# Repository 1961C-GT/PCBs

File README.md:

# PCBs
A Repo for storing all PCB designs for the project

# Library
All collaborative eagle library items should be stored in a .lbr file located in ./Libraries.

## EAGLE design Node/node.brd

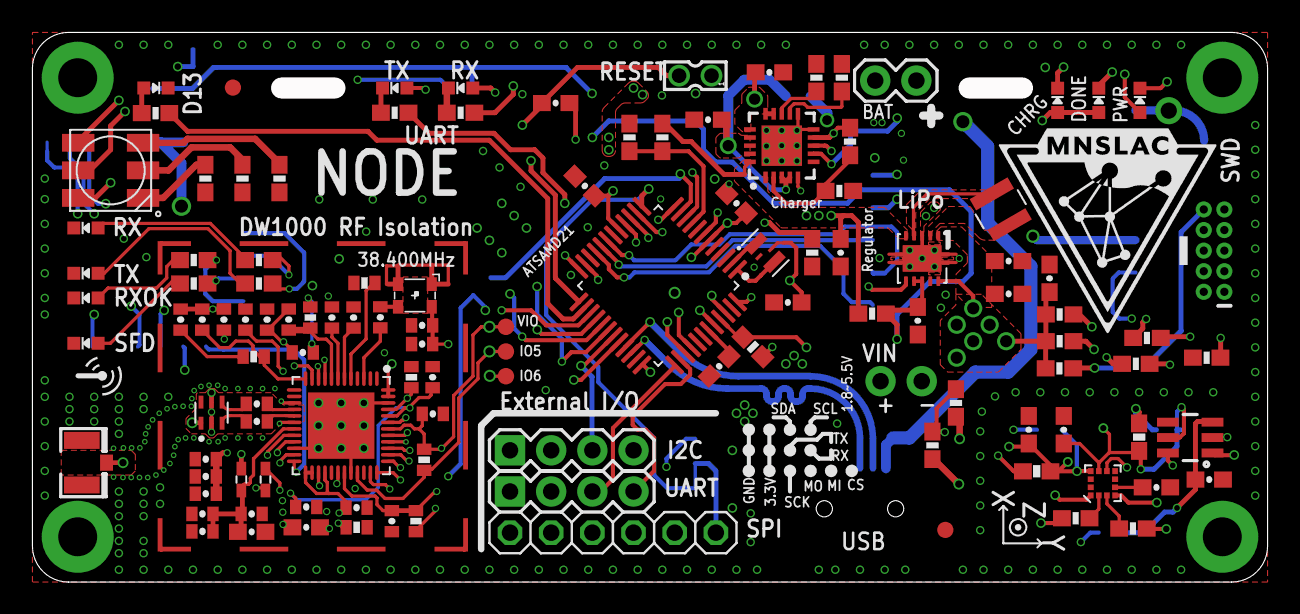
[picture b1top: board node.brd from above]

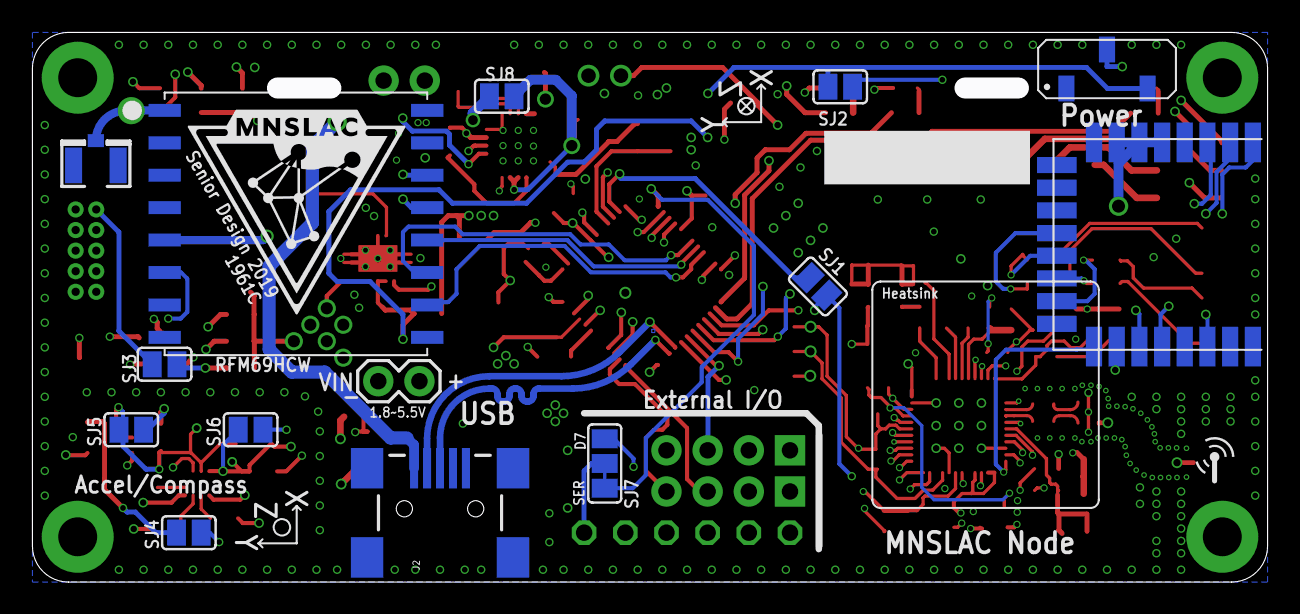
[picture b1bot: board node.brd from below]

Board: 4 copper layers, 76.2 x 33.9 mm, 143 parts (17 on the bottom side), 99 nets.

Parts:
BALUN1: HHM1595A1; BALUN_HHM1595A1
BOTTOM-LOGO: MNSLAC0.25; MNSLAC-0.25
C1, C36: 1uF; 0603-CAP
C2, C32, C37, C38, C39, C40, C41: 0.1uF; 0603-CAP
C3, C4, C5, C7, C8, C9, C10, C11, C12, C20, C21, C25, C29, C35: 0.1uF; 0402-CAP
C6, C17, C22, C30, C33, C43, C44: 10uF; 0603-CAP
C13, C14: 12pf; 0402-CAP
C15: 18pF; 0402-CAP
C16: 820pF; 0402-CAP
C18: 1.2pF; 0402-CAP
C19: 27pF; 0402-CAP
C23, C27: 12nF; 0402-CAP
C24, C28: 330nF; 0402-CAP
C26, C31: 22uF; 0603-CAP
C34: 2200pF; 0402-CAP
CHRG: YELLOW; CHIPLED_0603_NOOUTLINE
D13: YELLOW; CHIPLED_0603_NOOUTLINE
DONE: GREEN; CHIPLED_0603_NOOUTLINE
FID3, FID4: FIDUCIAL""; FIDUCIAL_1MM
I2C: 1X04
J1, J3: U.FL
J2: USBSMD; USB-MINIB
J4, J6: 1X02
J5: CORTEX_DEBUGPTH; 2X5-PTH-1.27MM
JP2: 1X01_ROUND
L1, L2: BLM15AG601SN1D; WE-CBA_0402(W=2.2)
L3: 2.2uH; 1212IND
LED1: RGBLED5050
PWR: RED; CHIPLED_0603_NOOUTLINE
PWR_SW: SWITCH_SPDTJS102011JCQN; JS102011JCQN
R1, R2, R3, R5, R12, R15, R16, R18, R19, R21, R22, R23, R31: 470; 0603-RES
R4: 16K; 0402-RES
R6: 11K 1%; 0402-RES
R7: 22K; 0402-RES
R8, R9: UNUSED-10K; 0402-RES
R10: 270; 0402-RES
R11: 16k; 0402-RES
R13: 270K; 0603-RES
R14, R28, R35, R38, R39: 100K; 0603-RES
R17, R36: 1K; 0603-RES
R20: 22K; 0603-RES
R24: 100; 0603-RES
R26, R27, R33: 4.7K; 0603-RES
R29, R30, R32, R34: 10K; 0603-RES
RT2: 10K; 0603-RES
RX: CHIPLED_0603_NOOUTLINE
RXOK: CHIPLED_0603_NOOUTLINE
SFD: CHIPLED_0603_NOOUTLINE
SJ1, SJ2, SJ3, SJ4, SJ5, SJ6, SJ8: SJ
SJ7: SJ_2
SPI: 1X06
TOP-LOGO: MNSLAC0.25; MNSLAC-0.25
TP1, TP2, TP3-OTP: TEST-POINT3X4; PAD.03X.04
TP3, TP4: VDD_TP; TP_15TH
TX: CHIPLED_0603_NOOUTLINE
U1: MCP73871; QFN20_4MM
U2: DW1000-I; QFN40P600X600X90-49T410
U3: RFM69HCW; RFMHCW_SMT
U4: SAMD21G18A-AUTTQFN48; QFP50P900X900X120-48
U5: LSM303C; LGA-12
U6: LM3880; SOT23-6
U7: DWM1000
U$1: FOUR_LAYER_WARNING
U$3: RF-SHIELD-COVER-SMS-255F; RF-SHIELD-COVER
U$6: RF-SHIELD; SMS-255F
U$7: HEATSINK; LTN20069
U$11: 38.400MHz; ASTXR-12
U$12: 3.3V; 10-VFDFNEXPOSEDPAD
U$15, U$23: RFLOGO0.1; RFLOGO-0.1
U$29: 32.768kHz; MEMS4-SMD
U$40, U$43: ZIPTIE
UART: 1X04
UARTRX: GREEN; CHIPLED_0603_NOOUTLINE
UARTTX: RED; CHIPLED_0603_NOOUTLINE
X2: 332-02

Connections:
3.3V: C2.1, C3.1, C21.1, C26.2, C30.1, C33.1, C35.2, C37.2, C38.2, C43.1, C44.1, I2C.2, J5.1, L1.2, L2.2, PWR.A, R28.1, R33.1, R35.1, R36.2, R38.2, R39.2, SJ4.2, SJ5.2, SJ6.2, SPI.2, U2.15, U2.25, U2.26, U2.28, U2.47, U2.48, U3.5P, U4.6, U4.17, U4.36, U4.44, U6.1, U7.5, U7.6, U7.7, U$11.P$6, U$12.PX1, U$12.PX10, U$29.P4, UART.2, UARTRX.A, UARTTX.A
!CS_MAG: R30.2, U5.3
!CS_XL: R29.2, U5.2
!DWRST: SJ1.2, U2.27, U7.3
!DWRSTSAMD: SJ1.1, U4.11
!EXTCS: SJ7.1, U4.12
!EXTCSCOM: SJ7.2, SJ7.3, SPI.6, U4.13
!RESET: C37.1, R33.2, SJ3.2, U4.40, X2.2
!RFMCS: R38.1, U3.13P
!RFMRST: R39.1, U3.14P, U4.10
!SPICS: U2.24, U4.27, U7.17
ANT: BALUN1.1, J1.3
BAL_N: BALUN1.3, C14.1
BAL_P: BALUN1.4, C13.1
BLU: LED1.3, U4.30
CLKTUNE: C18.2, R11.2, U2.8
D13LED: R21.1, U4.26
D+: J2.D+, U4.34
D-: J2.D-, U4.33
EXTON: U2.21, U4.28, U7.1
GND: BALUN1.2, BALUN1.5, C1.2, C2.2, C3.2, C4.2, C5.2, C6.2, C7.2, C8.2, C9.2, C10.2, C11.2, C12.2, C17.2, C20.1, C21.2, C22.2, C23.2, C24.2, C25.2, C26.1, C27.2, C28.2, C29.2, C30.2, C31.2, C32.2, C33.2, C35.1, C36.1, C38.1, C39.2, C40.1, C41.2, C43.2, C44.2, D13.C, I2C.1, J1.1, J1.2, J2.GND, J2.MTN1, J2.MTN2, J2.MTN3, J2.MTN4, J3.1, J3.2, J4.1, J5.3, J5.5, J5.9, J6.1, PWR_SW.P$1, R1.1, R2.1, R3.1, R4.2, R6.1, R7.1, R14.2, R17.1, R20.1, R22.2, R34.1, RT2.1, RX.C, RXOK.C, SFD.C, SPI.1, TX.C, U1.P$10, U1.P$11, U1.P$21, U2.22, U2.32, U2.43, U2.46, U2.49, U3.2P, U3.9P, U3.16P, U4.5, U4.18, U4.35, U4.42, U5.6, U5.8, U6.2, U7.8, U7.16, U7.21, U7.23, U7.24, U$6.P$1, U$6.P$2, U$6.P$3, U$6.P$4, U$6.P$5, U$6.P$6, U$6.P$7, U$6.P$8, U$6.P$9, U$6.P$10, U$6.P$11, U$6.P$12, U$6.P$13, U$6.P$14, U$6.P$15, U$6.P$16, U$11.P$1, U$11.P$3, U$12.PAD@1, U$12.PX3, U$12.PX9, U$29.P2, UART.1, X2.1
GPIO0: R19.1, U2.38, U7.15
GPIO1: R18.1, U2.37, U7.14
GPIO2: R12.1, U2.36, U7.13
GPIO3: R5.1, U2.35, U7.12
GPIO5: R8.2, TP1.P$1, U2.33
GPIO6: R9.2, TP2.P$1, U2.30
GRN: LED1.1, U4.24
IRQ: R7.2, U2.45, U4.23, U7.22
LIPOADC: R32.1, R34.2, U4.9
LSMDELAY: C39.1, R28.2, SJ5.1, TP3.P$1, U5.9, U6.5
LSMVDDIO: C41.1, R26.2, R27.2, R29.1, R30.1, R35.2, SJ6.1, TP4.P$1, U5.10, U6.6
MISO: U2.40, U3.10P, U4.21, U7.19
MISO_EXT: SPI.5, U4.14
MOSI: U2.39, U3.11P, U4.19, U7.18
MOSI_EXT: SPI.4, U4.15
unnamed: J5.10, SJ3.1
unnamed: LED1.5, R1.2
unnamed: LED1.6, R2.2
unnamed: LED1.4, R3.2
unnamed: R5.2, TX.A
unnamed: R12.2, RX.A
unnamed: C16.2, R10.1
unnamed: R13.1, R14.1, U1.P$2
unnamed: R23.2, UARTRX.C
unnamed: C5.1, C10.1, U2.20, U2.44
unnamed: R16.1, U1.P$7
unnamed: R15.1, U1.P$8
unnamed: RT2.2, U1.P$5
unnamed: C19.2, R11.1
unnamed: DONE.C, R16.2
unnamed: R17.2, U1.P$13
unnamed: CHRG.C, R15.2
unnamed: R20.2, U1.P$12
unnamed: C36.2, SJ4.1, U6.3
unnamed: R18.2, SFD.A
unnamed: PWR.C, R22.1
unnamed: L3.P2, U$12.PX4
unnamed: R19.2, RXOK.A
unnamed: C34.1, U2.3
unnamed: C34.2, U$11.P$4
unnamed: U4.2, U$29.P1
unnamed: C40.2, U5.5
unnamed: L3.P1, U$12.PX2
unnamed: PWR_SW.P$2, SJ2.2, U$12.PX6
unnamed: D13.A, R21.2
unnamed: R31.2, UARTTX.C
unnamed: C1.1, U4.43
unnamed: C32.1, PWR_SW.P$3, R24.1, SJ2.1, U$12.PX7, U$12.PX8
unnamed: U4.1, U$29.P3
unnamed: J3.3, JP2.1, U3.1P
RED: LED1.2, U4.25
RFMIQR: U3.6P, U4.7
RF_N: C14.2, U2.17
RF_P: C13.2, U2.16
RXD: U4.38, UART.4
RXLED: R23.1, U4.48
SCK: U2.41, U3.12P, U4.20, U7.20
SCK_EXT: SPI.3, U4.16
SCL: I2C.4, R26.1, U4.32, U5.1
SDA: I2C.3, R27.1, U4.31, U5.4
SWCLK: J5.4, R36.1, U4.45
SWDIO: J5.2, U4.46
TXD: U4.37, UART.3
TXLED: R31.1, U4.39
VBUS: C6.1, CHRG.A, DONE.A, J2.VBUS, R13.2, SJ8.1, U1.P$3, U1.P$4, U1.P$9, U1.P$17, U1.P$18, U1.P$19
VCC-ISO: C22.1, J6.2, R24.2, R32.2, SJ8.2, U1.P$1, U1.P$20, U$12.PX5
VCOTUNE: C15.2, R10.2, U2.12
VDDCLK: C7.1, C18.1, C19.1, U2.9
VDDIF: C9.1, U2.7
VDDIO: C4.1, C20.2, R8.1, R9.1, TP3-OTP.P$1, U2.31, U2.42
VDDMS: C8.1, U2.6
VDDPA1: C23.1, C24.1, C25.1, L1.1, U2.18
VDDPA2: C27.1, C28.1, C29.1, C31.1, L2.1, U2.19
VDDSYN: C12.1, U2.10
VDDVCO: C11.1, C15.1, C16.1, U2.11
VLIPO: C17.1, J4.2, U1.P$14, U1.P$15, U1.P$16
VREF: R6.2, U2.5
WAKEUP: R4.1, U2.23, U4.29, U7.2

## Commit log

2019-01-17 Initial commit. Added Libraries folder and the Node PCB folder. Created starter schematic and board.
2019-01-22 Work on the DW1000 SCH
2019-01-23 Added gitignore for eagle
2019-01-23 Added some required ground connections
2019-01-23 More work on schematic, documentation, frame, shielding, etc.
2019-01-24 Moved the RF components to an area that will be covered by the RF shield. Also went through two sources and confirmed SCH and BRD layout for the DW1000 (specifically with respect to caps and resistor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
2019-01-24 Added logos and test board layout for logo testing
2019-01-24 Added the RF Shield to the sch and brd, then routed all components of the current schematic
2019-01-24 Added IRQ to an ATMEGA Int pin, isolated !RST behind a solder bubble
2019-01-24 Added TX and RX leds for the DW1000
2019-01-24 Moved the antenna such that the impedance lines are parallel and straight. Also added internal ground plane isolation for the buried antenna wire
2019-01-26 Added SCH components for charging and regulation. Calculated resistor values needed for the regulator
2019-01-30 Added the inductor Lib item. Also made a few changes to the ATMEGA Pin assignments to match the breadboarded Radio/Arduino setup
2019-01-30 Added external TCXO Oscillator to schematic
2019-01-30 Created the CP2105 Lib device (Cheap FTDI Clone). Also changed the charging IC to one that includes battery protection.
2019-01-30 Changed the size of the board to match the likely enclosure size.
2019-01-30 RF work, framing, and finish layer
2019-01-31 More RF work. Increased the RF shield size, routed TCXO.
2019-01-31 Added RF exposed plane to the stop layers as well
2019-01-31 Removed unneeded JST connector
2019-01-31 Routed LEDs near side wall. Changed overall size. Added heatsink. Created an exposed-copper version of the logo.
2019-01-31 Added CP2105 FTDI chip
2019-02-01 Added sram chip, compass, buck/boost converter, lipo charger. DRC checks. Cosmetic changes.
2019-02-01 Created SAMD21 branch
2019-02-01 Initial commit with new schematic and general board layout.
2019-02-01 Finished initial routing, schematic and silkscreen pass. Ready for review.
2019-02-01 Minor modifications
2019-02-02 Part modifications, added part numbers to all parts (except resistors and capicators). Library consolidation.
2019-02-02 Resistor documentation
2019-02-03 Prep to move to a new power regulator, as previous one is only boost
2019-02-03 Initial pass of the new regulator circuit. Passes DRT.
2019-02-03 Changes to the regulater schematic
2019-02-04 Added RFM69HCW slot for possible use for base-station communications. Routed external SPI slot to SERCOM 2 Alt so the ATSAMD21 can be used as an SPI slave for the RPi (to gather data from the network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
2019-02-04 Refinement, checking components, etc.
2019-02-04 Updated the DW1000 Footprint per its datasheet
2019-02-04 Reworked the ATSMD21 package
2019-02-04 Detailed changes, small stuff. Checking everything over. Switched to the new SAMD21 package.
2019-02-04 Updated the SAMD21G lib item to add voltage tolerances
2019-02-04 Set the pin modes on the SAMD21G lib (IO/PWR)
2019-02-04 Switched clocks to a new library item, allowing for the ATSAMD21 RTC to use XTAL crystal for reduced cost. Verious small modifications
2019-02-05 Other minor changes. Push before moving to a different battery
2019-02-06 Moved USB to another edge, moved SWD to the bottom edge, added the DWM1000 module pads just in case.
2019-02-06 Cleaned up silkscreen
2019-02-06 Final changes, prep for order
2019-02-06 Added copper logo
2019-02-06 Folder organizing
2019-02-06 Finishing touches
2019-02-06 Moved VDD wire for DWM1000 to allow for easier reflow
2019-02-06 Updated DW1000 crystal because the old one was non-stocked now.
2019-02-07 Final (hopefully) commit for the board order
2019-02-07 Added CAM results

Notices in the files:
parts and their libraries:
SparkFun-Capacitors: Licensing: Creative Commons ShareAlike 4.0 International - https://creativecommons.org/licenses/by-sa/4.0
